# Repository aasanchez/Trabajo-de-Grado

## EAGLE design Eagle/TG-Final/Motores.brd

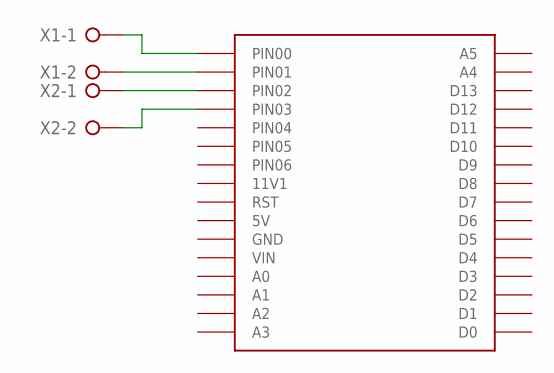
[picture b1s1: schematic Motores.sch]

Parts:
U$1: BASE-FINAL
X1, X2: W237-02P; W237-132

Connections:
unnamed: U$1.PIN01, X1.2
unnamed: U$1.PIN02, X2.1
unnamed: U$1.PIN03, X2.2
unnamed: U$1.PIN00, X1.1

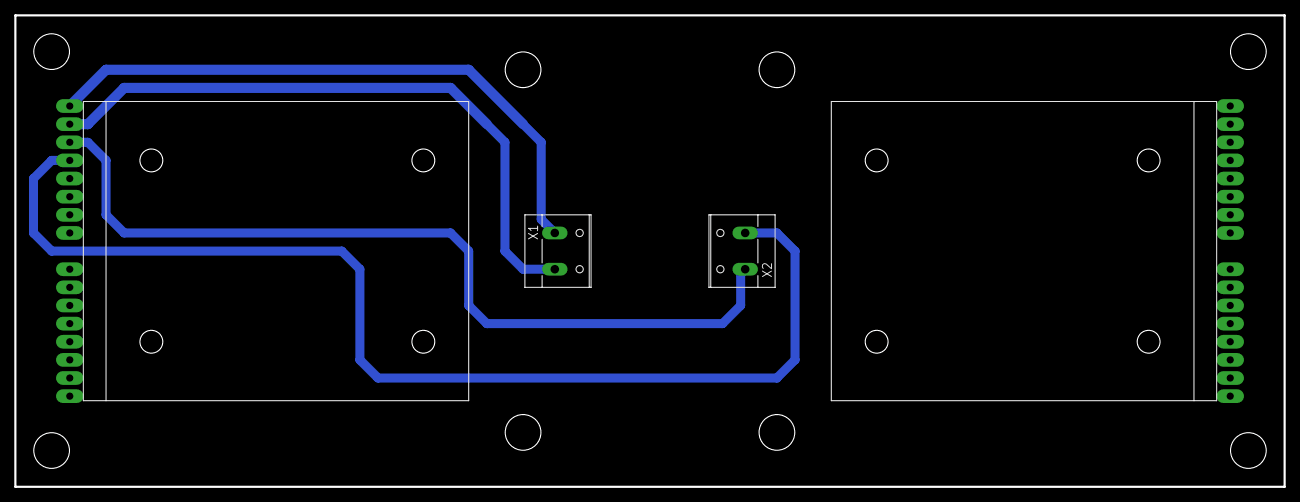
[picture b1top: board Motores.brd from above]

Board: 2 copper layers, 177.8 x 66.0 mm, 5 parts (0 on the bottom side), 4 nets.

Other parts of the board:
U$2, U$3: BASEMOTOR

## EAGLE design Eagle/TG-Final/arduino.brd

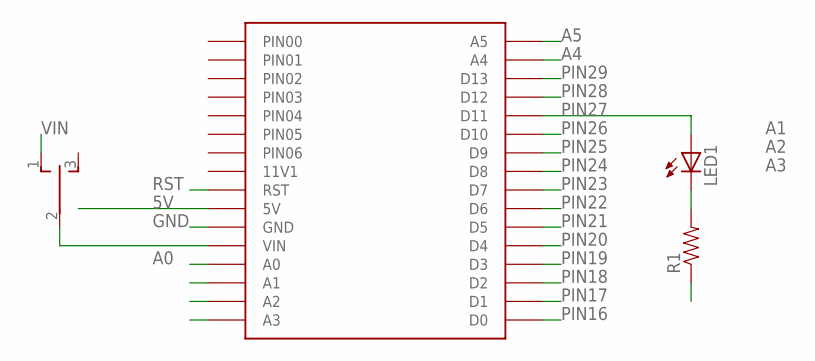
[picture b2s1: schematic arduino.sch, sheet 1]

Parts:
LED1: LED3MM
R1: RESISTORKIT; AXIAL-0.3-KIT
S2: TL39YOSWITCH_2_ESTADOS; TL3XYO
U$1: BASE-FINAL

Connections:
5V: U$1.5V; also elsewhere on the board
A0: U$1.A0; also elsewhere on the board
A1: U$1.A1; also elsewhere on the board
A2: U$1.A2; also elsewhere on the board
A3: U$1.A3; also elsewhere on the board
A4: U$1.A4; also elsewhere on the board
A5: U$1.A5; also elsewhere on the board
GND: R1.P$1 (1), U$1.GND; also elsewhere on the board
unnamed: S2.2, U$1.VIN
unnamed: LED1.K (C), R1.P$2 (2)
PIN16: U$1.0 (D0); also elsewhere on the board
PIN17: U$1.1 (D1); also elsewhere on the board
PIN18: U$1.2 (D2); also elsewhere on the board
PIN19: U$1.3 (D3); also elsewhere on the board
PIN20: U$1.4 (D4); also elsewhere on the board
PIN21: U$1.5 (D5); also elsewhere on the board
PIN22: U$1.6 (D6); also elsewhere on the board
PIN23: U$1.7 (D7); also elsewhere on the board
PIN24: U$1.8 (D8); also elsewhere on the board
PIN25: U$1.9 (D9); also elsewhere on the board
PIN26: U$1.10 (D10); also elsewhere on the board
PIN27: LED1.A, U$1.11 (D11); also elsewhere on the board
PIN28: U$1.12 (D12); also elsewhere on the board
PIN29: U$1.13 (D13); also elsewhere on the board
RST: U$1.RST; also elsewhere on the board
VIN: S2.1 (O); also elsewhere on the board

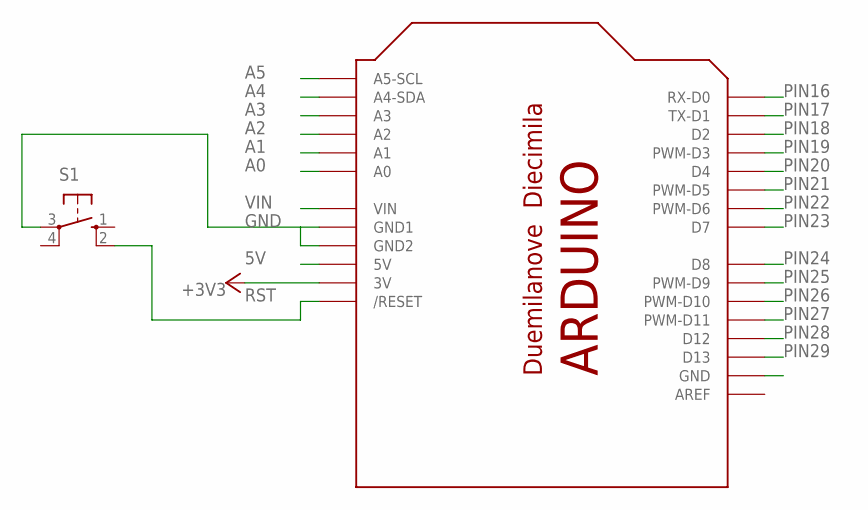
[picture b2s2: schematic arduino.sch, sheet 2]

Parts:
S1: 10-XX; B3F-10XX
U$6: ARDUINO-NOHOLE

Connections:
5V: U$6.5V; also elsewhere on the board
+3V3: U$6.3V; also elsewhere on the board
A0: U$6.A0; also elsewhere on the board
A1: U$6.A1; also elsewhere on the board
A2: U$6.A2; also elsewhere on the board
A3: U$6.A3; also elsewhere on the board
A4: U$6.A4 (A4-SDA); also elsewhere on the board
A5: U$6.A5 (A5-SCL); also elsewhere on the board
GND: S1.3, U$6.GND, U$6.GND1, U$6.GND2; also elsewhere on the board
PIN16: U$6.D0 (RX-D0); also elsewhere on the board
PIN17: U$6.D1 (TX-D1); also elsewhere on the board
PIN18: U$6.D2; also elsewhere on the board
PIN19: U$6.D3 (PWM-D3); also elsewhere on the board
PIN20: U$6.D4; also elsewhere on the board
PIN21: U$6.D5 (PWM-D5); also elsewhere on the board
PIN22: U$6.D6 (PWM-D6); also elsewhere on the board
PIN23: U$6.D7; also elsewhere on the board
PIN24: U$6.D8; also elsewhere on the board
PIN25: U$6.D9 (PWM-D9); also elsewhere on the board
PIN26: U$6.D10 (PWM-D10); also elsewhere on the board
PIN27: U$6.D11 (PWM-D11); also elsewhere on the board
PIN28: U$6.D12; also elsewhere on the board
PIN29: U$6.D13; also elsewhere on the board
RST: S1.2 (S1), U$6.RESET (/RESET); also elsewhere on the board
VIN: U$6.VIN; also elsewhere on the board

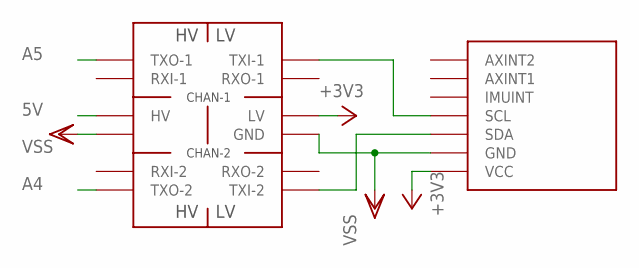
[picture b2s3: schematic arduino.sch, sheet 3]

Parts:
U$7: IMU3000COMBO; IMU3000-COMBO
U$8: LOGIC-LEVEL-CONVERTER; LEVEL-CONVERTER

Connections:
5V: U$8.P$10 (HV); also elsewhere on the board
+3V3: U$7.3V3 (VCC), U$8.P$3 (LV); also elsewhere on the board
A4: U$8.P$7 (TXO-2); also elsewhere on the board
A5: U$8.P$12 (TXO-1); also elsewhere on the board
GND: U$7.VSS (GND), U$8.P$4 (GND), U$8.P$9; also elsewhere on the board
unnamed: U$7.SCL, U$8.P$1 (TXI-1)
unnamed: U$7.SDA, U$8.P$6 (TXI-2)

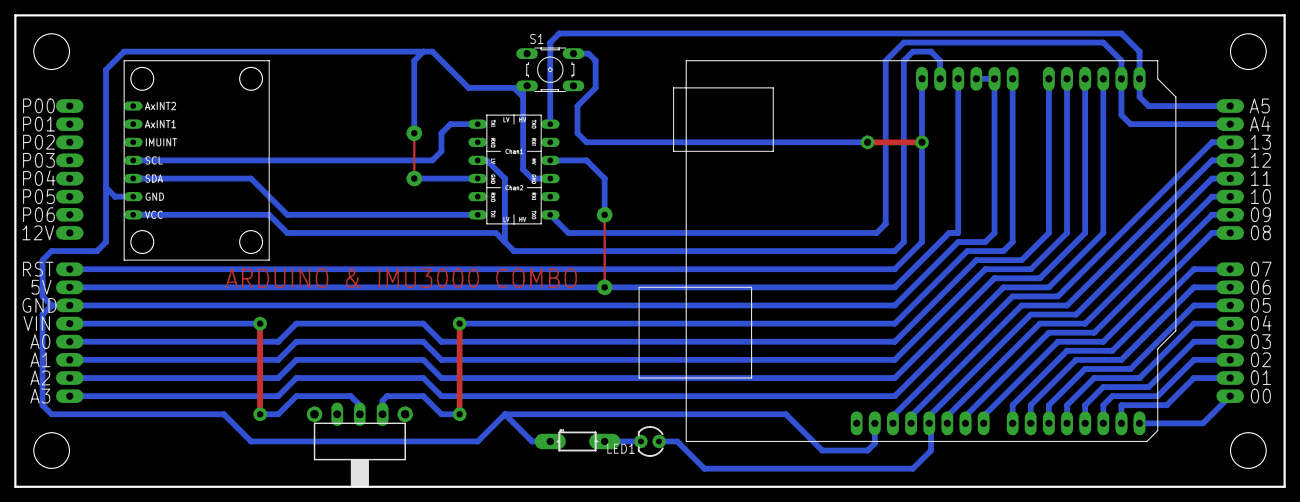
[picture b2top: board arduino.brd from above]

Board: 2 copper layers, 177.8 x 66.0 mm, 8 parts (1 on the bottom side), 29 nets.

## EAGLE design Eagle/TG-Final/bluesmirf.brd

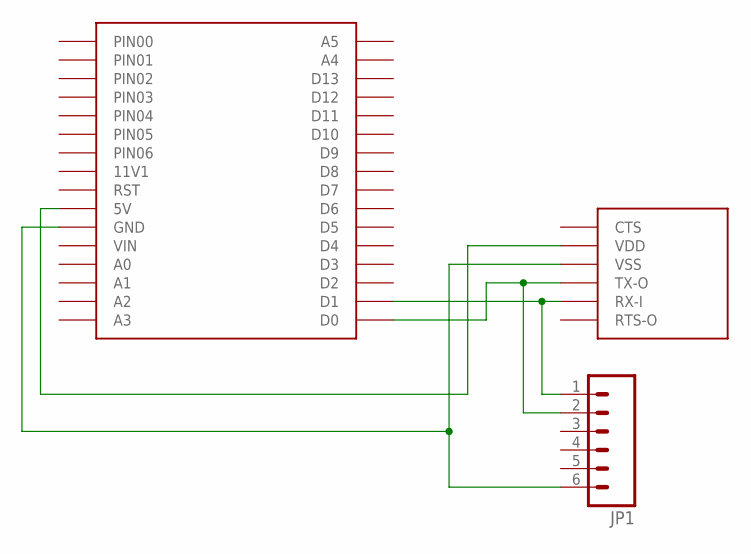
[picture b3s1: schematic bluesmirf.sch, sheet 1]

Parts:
JP1: M06LONGPADS; 1X06_LONGPADS
U$1: BASE-FINAL
U$2: BLUESMIRF

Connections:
unnamed: U$1.5V, U$2.VDD
unnamed: JP1.6, U$1.GND, U$2.VSS
unnamed: JP1.2, U$1.0 (D0), U$2.TX-O
unnamed: JP1.1, U$1.1 (D1), U$2.RX-I

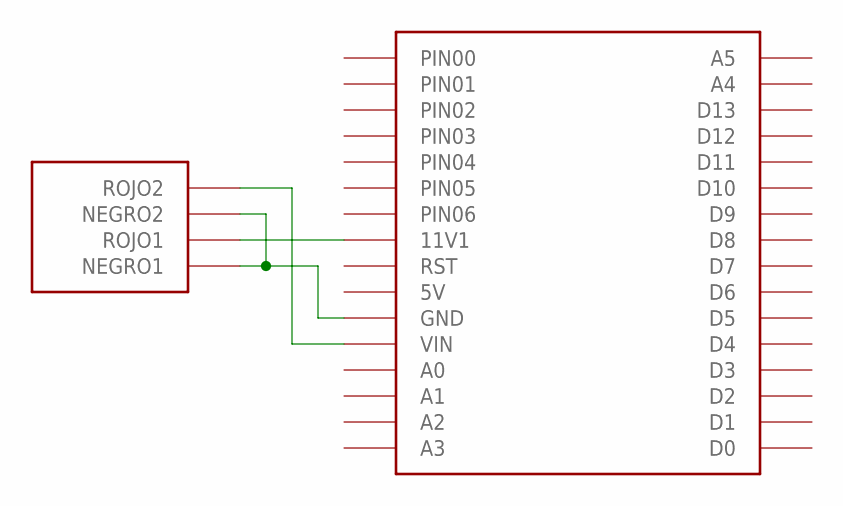
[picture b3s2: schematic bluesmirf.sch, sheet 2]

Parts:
U$3: BASE-FINAL
U$4: CONECTOR_AUDIO

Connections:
unnamed: U$3.GND, U$4.NEGRO1, U$4.NEGRO2
unnamed: U$3.12V (11V1), U$4.ROJO1
unnamed: U$3.VIN, U$4.ROJO2

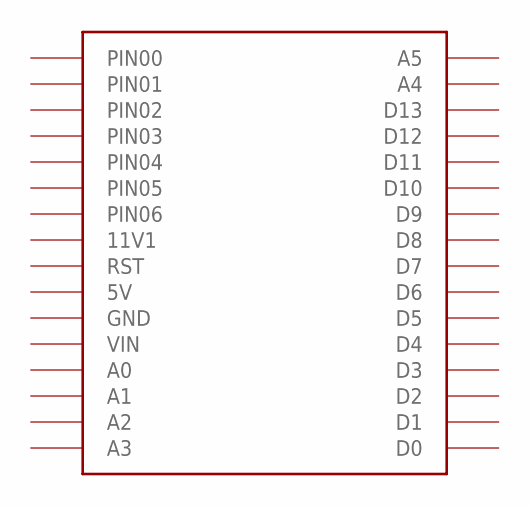
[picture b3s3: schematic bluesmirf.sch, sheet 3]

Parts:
U$7: BASE-FINAL

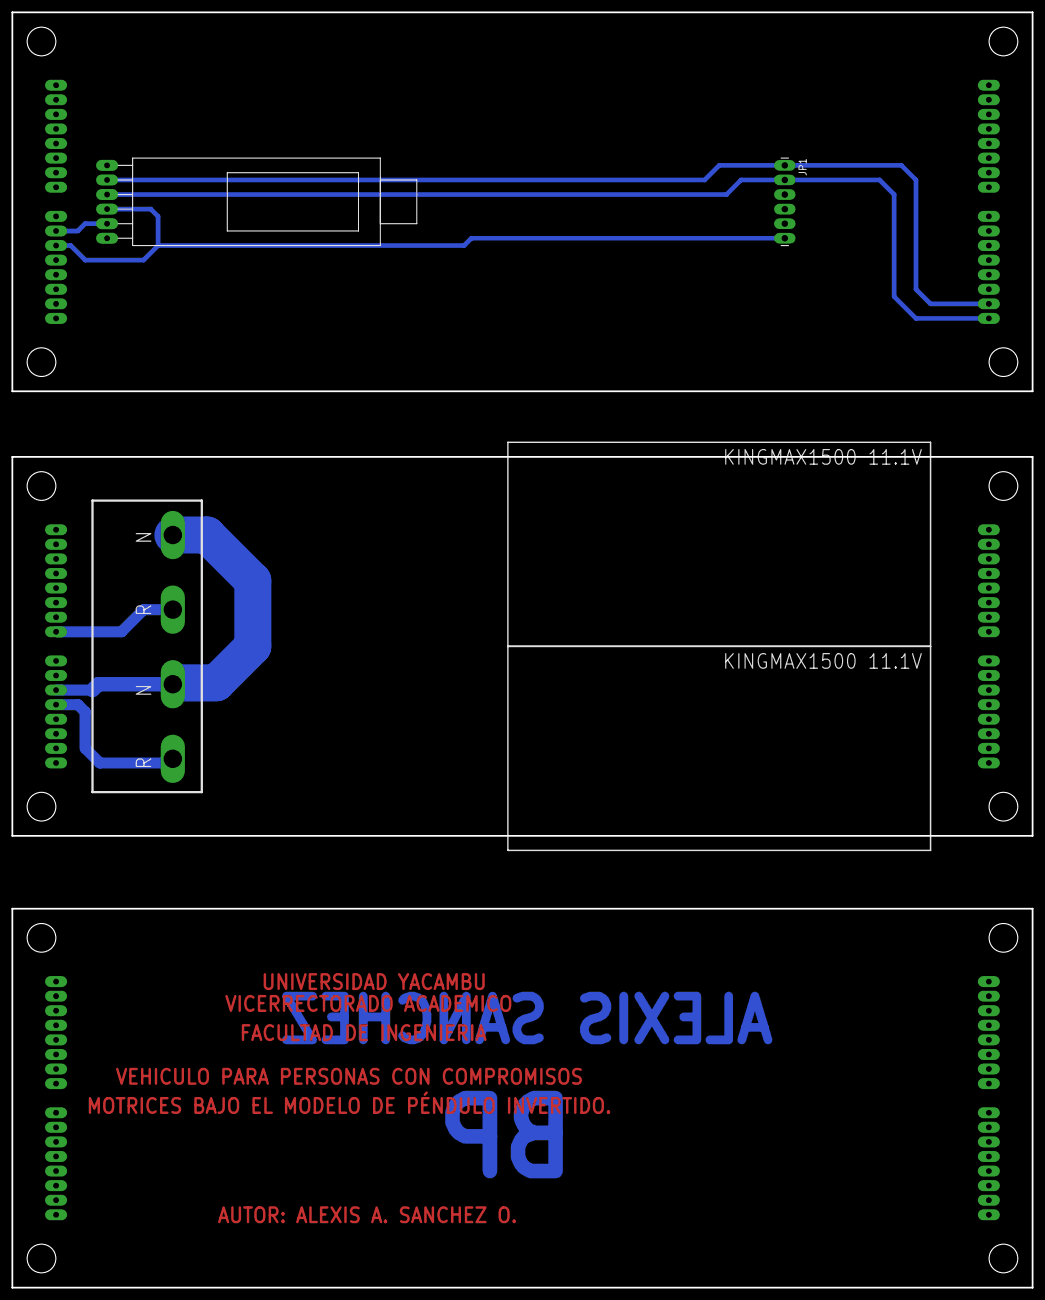
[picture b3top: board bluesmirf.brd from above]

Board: 2 copper layers, 177.8 x 222.2 mm, 8 parts (0 on the bottom side), 7 nets.

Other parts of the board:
U$5, U$6: KINGMAX1500H

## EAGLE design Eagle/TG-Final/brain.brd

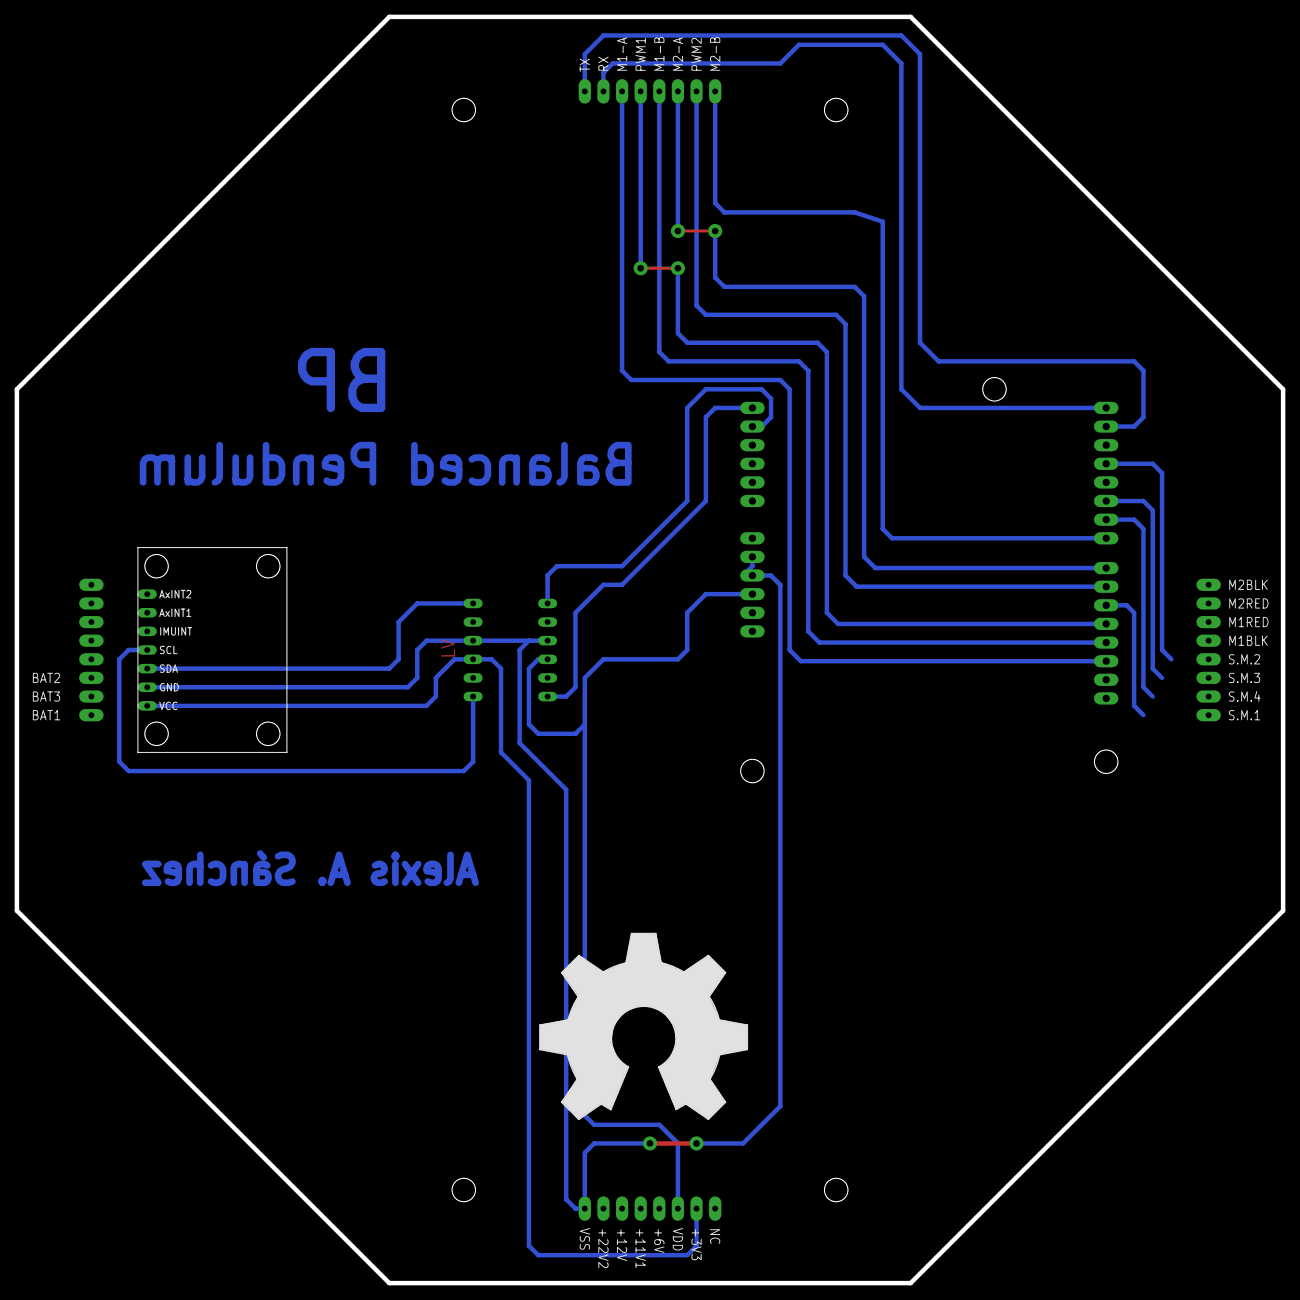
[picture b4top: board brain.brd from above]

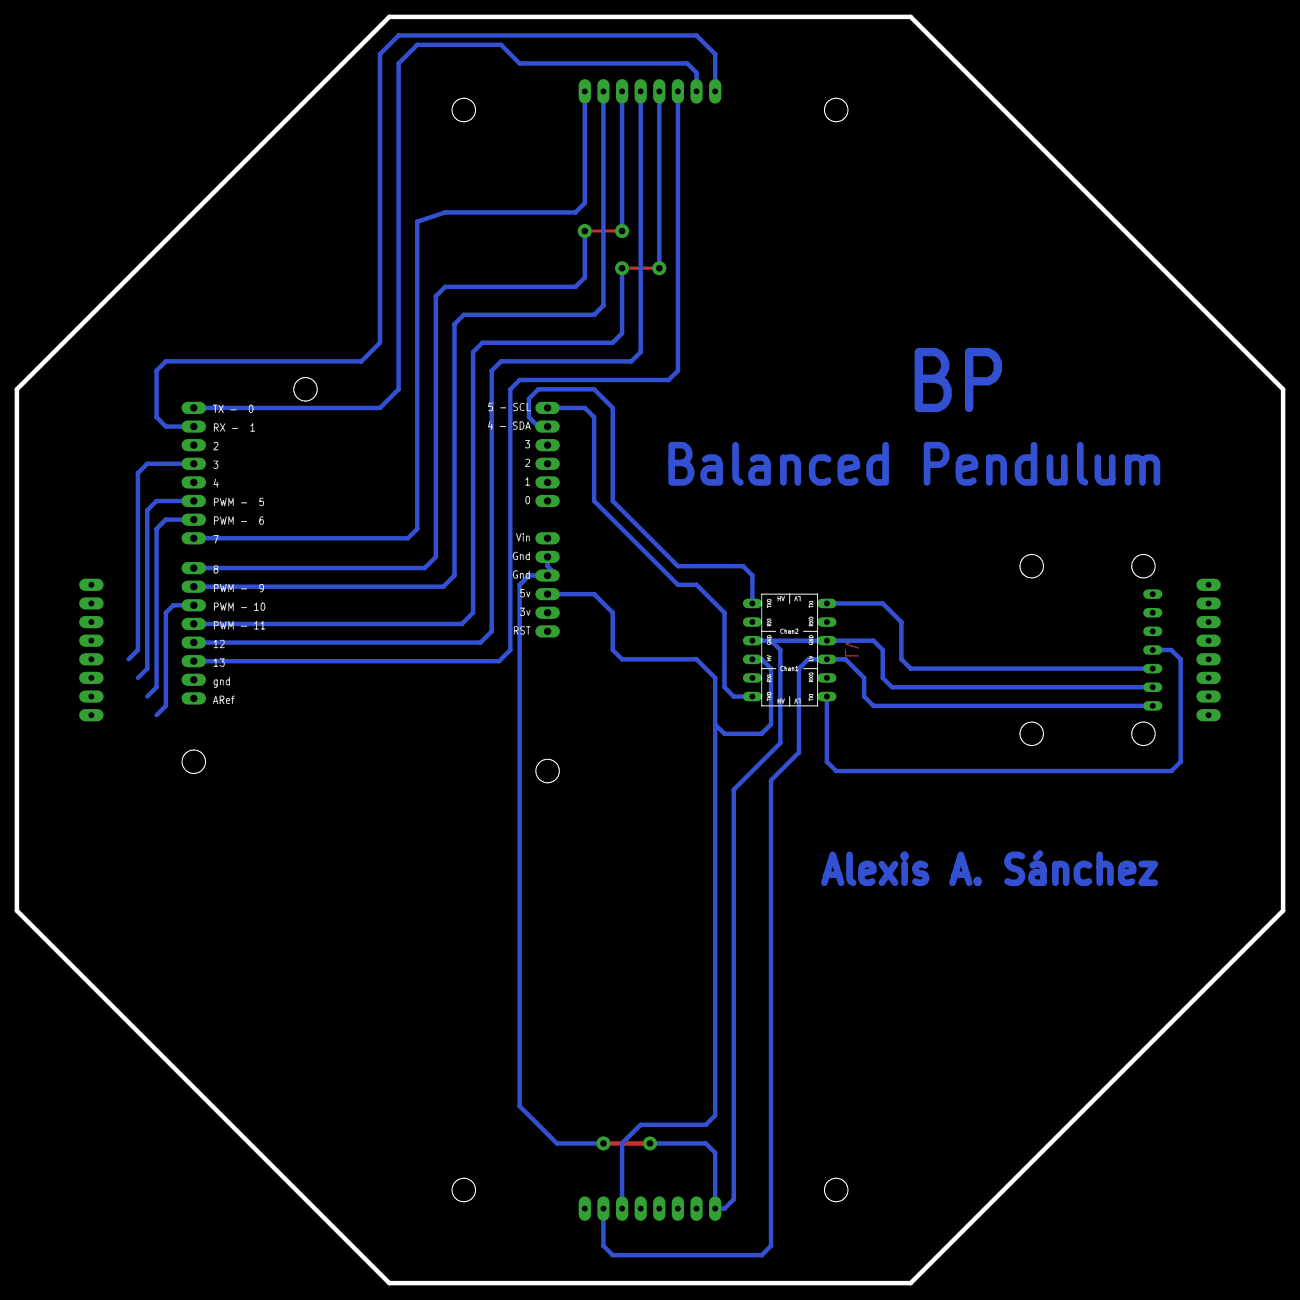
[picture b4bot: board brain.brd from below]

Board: 2 copper layers, 172.7 x 172.7 mm, 5 parts (2 on the bottom side), 15 nets.

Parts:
U$1: BASE
U$3: OSHW_FILLX1000_NOTEXT
U$6: ARDUINOUNO; ARDUINO
U$7: IMU3000COMBO; IMU3000-COMBO
U$8: LOGIC-LEVEL-CONVERTER; LEVEL-CONVERTER

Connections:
+3V3: U$1.PIN22, U$7.3V3, U$8.P$3
M1-A: U$1.PIN05, U$6.D13
M1-B: U$1.PIN03, U$6.D12
M2-A: U$1.PIN02, U$6.D8
M2-B: U$1.PIN00, U$6.D7
unnamed: U$7.SCL, U$8.P$1
unnamed: U$7.SDA, U$8.P$6
PWM1: U$1.PIN04, U$6.D11
PWM2: U$1.PIN01, U$6.D9
RX: U$1.PIN06, U$6.D0
SCL: U$6.A5, U$8.P$12
SDA: U$6.A4, U$8.P$7
TX: U$1.PIN07, U$6.D1
VDD: U$1.PIN21, U$6.5V, U$8.P$10
VSS: U$1.PIN16, U$6.GND1, U$6.GND2, U$7.VSS, U$8.P$4, U$8.P$9

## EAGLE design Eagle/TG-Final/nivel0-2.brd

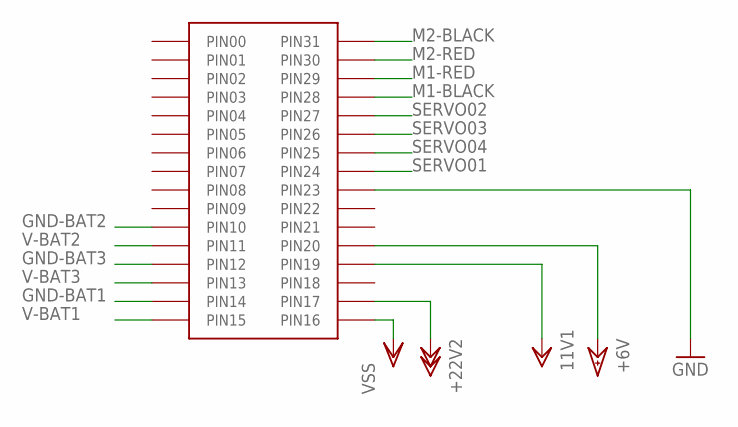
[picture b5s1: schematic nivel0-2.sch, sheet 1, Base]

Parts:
U$1: BASE

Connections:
+6V: U$1.PIN20; also elsewhere on the board
+11V1: U$1.PIN19; also elsewhere on the board
+22V: U$1.PIN17; also elsewhere on the board
GND: U$1.PIN23; also elsewhere on the board
GND-BAT1: U$1.PIN14; also elsewhere on the board
GND-BAT2: U$1.PIN10; also elsewhere on the board
GND-BAT3: U$1.PIN12; also elsewhere on the board
M1-BLACK: U$1.PIN28; also elsewhere on the board
M1-RED: U$1.PIN29; also elsewhere on the board
M2-BLACK: U$1.PIN31; also elsewhere on the board
M2-RED: U$1.PIN30; also elsewhere on the board
SERVO01: U$1.PIN24; also elsewhere on the board
SERVO02: U$1.PIN27; also elsewhere on the board
SERVO03: U$1.PIN26; also elsewhere on the board
SERVO04: U$1.PIN25; also elsewhere on the board
V-BAT1: U$1.PIN15; also elsewhere on the board
V-BAT2: U$1.PIN11; also elsewhere on the board
V-BAT3: U$1.PIN13; also elsewhere on the board
VSS: U$1.PIN16; also elsewhere on the board

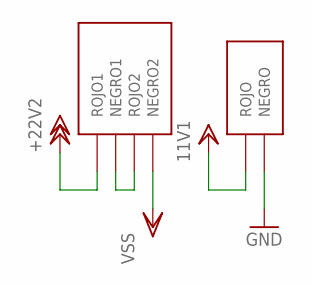
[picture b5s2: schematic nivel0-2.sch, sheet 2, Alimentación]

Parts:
U$11: CONECTOR_AUDIO
U$12: CONECTOR_AUDIO2

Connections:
+11V1: U$12.P$2 (ROJO); also elsewhere on the board
+22V: U$11.P$1 (ROJO1); also elsewhere on the board
GND: U$12.P$1 (NEGRO); also elsewhere on the board
unnamed: U$11.P$2 (NEGRO1), U$11.P$3 (ROJO2)
VSS: U$11.P$4 (NEGRO2); also elsewhere on the board

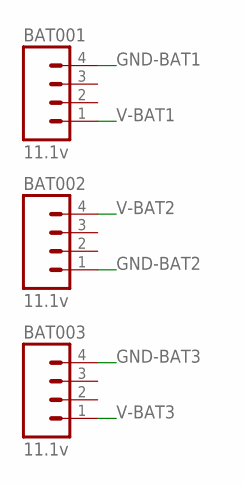
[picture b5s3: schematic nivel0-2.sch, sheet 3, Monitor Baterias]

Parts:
BAT001, BAT002, BAT003: 11.1v; 1X04_LONGPADS

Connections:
GND-BAT1: BAT001.4; also elsewhere on the board
GND-BAT2: BAT002.1; also elsewhere on the board
GND-BAT3: BAT003.4; also elsewhere on the board
V-BAT1: BAT001.1; also elsewhere on the board
V-BAT2: BAT002.4; also elsewhere on the board
V-BAT3: BAT003.1; also elsewhere on the board

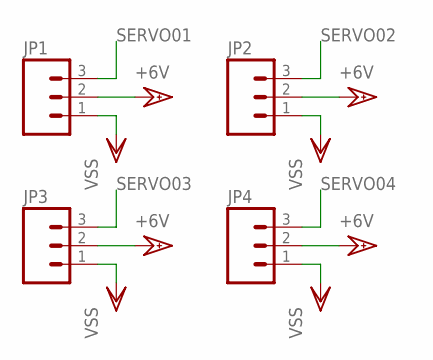
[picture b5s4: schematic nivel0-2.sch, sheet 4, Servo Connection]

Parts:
JP1, JP2, JP3, JP4: 1X03_LONGPADS

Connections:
+6V: JP1.2, JP2.2, JP3.2, JP4.2; also elsewhere on the board
SERVO01: JP1.3; also elsewhere on the board
SERVO02: JP2.3; also elsewhere on the board
SERVO03: JP3.3; also elsewhere on the board
SERVO04: JP4.3; also elsewhere on the board
VSS: JP1.1, JP2.1, JP3.1, JP4.1; also elsewhere on the board

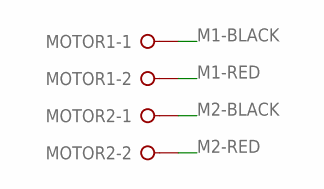
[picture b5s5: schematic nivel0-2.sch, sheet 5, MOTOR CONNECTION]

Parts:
MOTOR1, MOTOR2: W237-132

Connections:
M1-BLACK: MOTOR1.1; also elsewhere on the board
M1-RED: MOTOR1.2; also elsewhere on the board
M2-BLACK: MOTOR2.1; also elsewhere on the board
M2-RED: MOTOR2.2; also elsewhere on the board

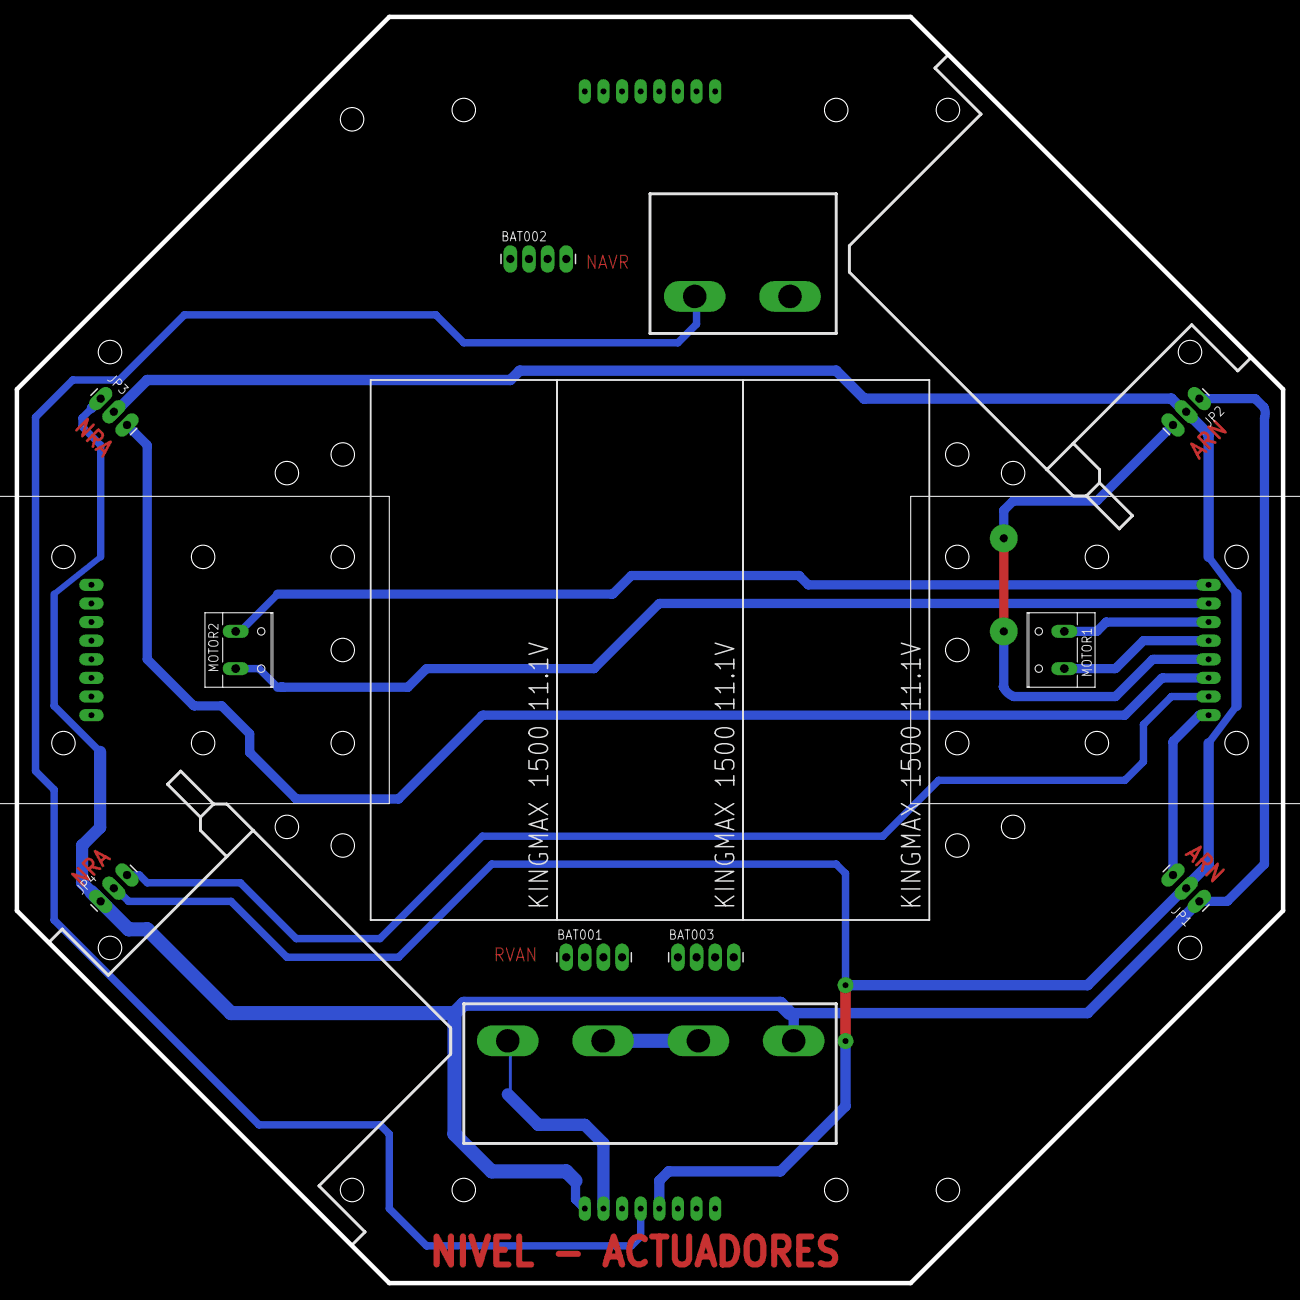
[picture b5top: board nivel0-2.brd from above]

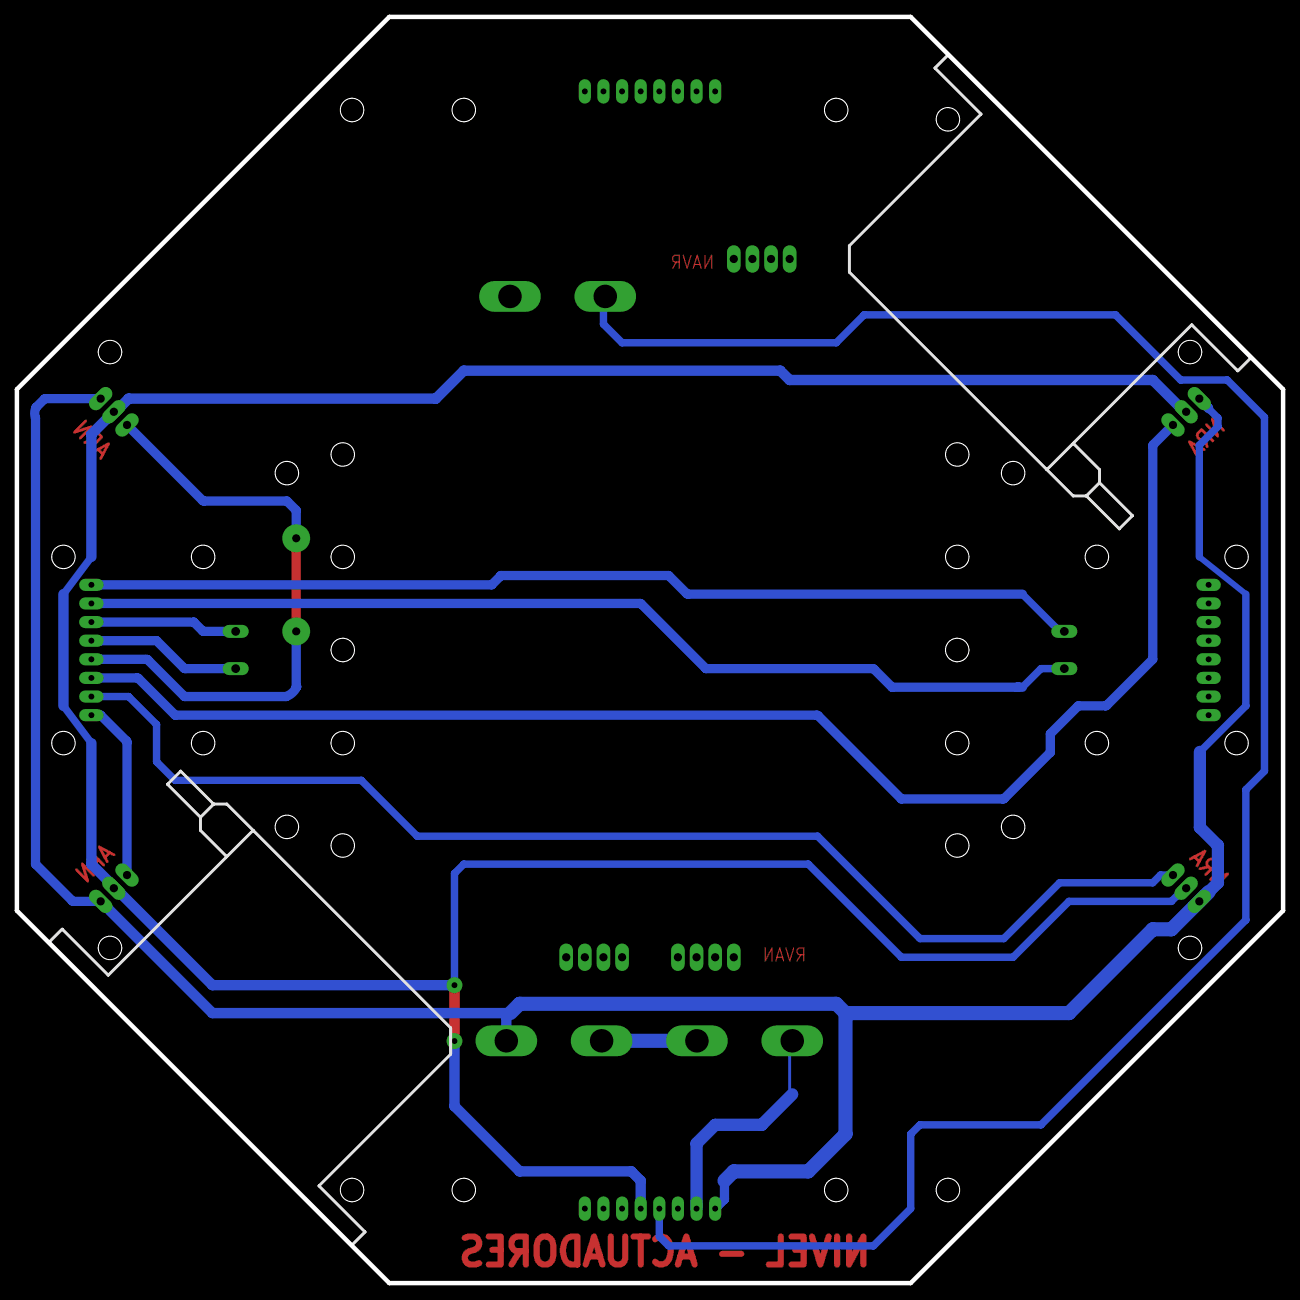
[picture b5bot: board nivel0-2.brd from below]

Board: 2 copper layers, 172.7 x 172.7 mm, 21 parts (2 on the bottom side), 20 nets.

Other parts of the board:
U$2, U$3, U$4: KINGMAX1500
U$5, U$6: BASEMOTOR
U$7, U$8, U$9, U$10: SERVOBODY

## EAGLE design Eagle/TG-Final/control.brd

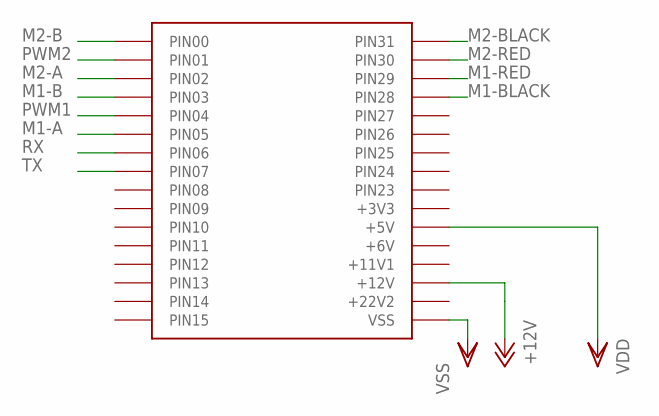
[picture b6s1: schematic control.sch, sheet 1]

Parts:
U$1: BASE

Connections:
+12V: U$1.PIN18 (+12V); also elsewhere on the board
M1-A: U$1.PIN05; also elsewhere on the board
M1-B: U$1.PIN03; also elsewhere on the board
M1-BLACK: U$1.PIN28; also elsewhere on the board
M1-RED: U$1.PIN29; also elsewhere on the board
M2-A: U$1.PIN02; also elsewhere on the board
M2-B: U$1.PIN00; also elsewhere on the board
M2-BLACK: U$1.PIN31; also elsewhere on the board
M2-RED: U$1.PIN30; also elsewhere on the board
PWM1: U$1.PIN04; also elsewhere on the board
PWM2: U$1.PIN01; also elsewhere on the board
RX: U$1.PIN06; also elsewhere on the board
TX: U$1.PIN07; also elsewhere on the board
VDD: U$1.PIN21 (+5V); also elsewhere on the board
VSS: U$1.PIN16 (VSS); also elsewhere on the board

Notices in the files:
parts and their libraries:
SparkFun: Licensing: CC v3.0 Share-Alike You are welcome to use this library for commercial purposes.
